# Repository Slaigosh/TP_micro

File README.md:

# TP_micro
# 1 Saisie du schéma
## 1.2 Le microcontrolleur sous KiCad
### Q13
PB9 est relié à la masse car c'est le pin boot0. 
Si le pin boot0 est relié à la masse, on boot dans la usermemory (notre code).
Si le pin boot0 est relié à Vdd, on boot dans la systemmemory (le bootloader).
Donc on veut boot dans notre code.

### Q14
L1, C5, C7 sont des composant de filtrage d'allimentation (données dans la datasheet).

## 1.3 Le reste du schéma
### Q3
Les données sont dans la page 3 de la datasheet, dans Recommended Operating Conditions.

### Q5
Les données sont dans la page 6 de la datasheet, dans AC Characteristics.

### Q6
La broche CS sert d'enable dans la communication SPI.

### Q7
C'est le pin de synchronisation du DAC.

### Q8
Il n'y a pas de MISO parce que le DAC ne communique pas au master

### Q10
C'est dans la datasheet du STLINKV3, page 19.

## 1.4 Affectation des empreintes
### Q3
0805, 009 et 1206 sont des tailles d'empreintes pour des composants passifs.
Par exemple, 0805 veut dire 8mm de longueur sur 5mm de largeur.

### Q4
LQFP, SOT-223 et SOIC sont des formes de boiter avec leur empreinte qui correspond.

# 2 Routage du circuit

# 3 Ecriture du firmware

## 3.1 Affectation des empreintes
### Q4
__STATIC_INLINE se met avant une fonction pour indiquer au compilateur de remplacer les appels de la fonction par le contenu de la fonction ( c'est comme une focntion macro).

### Q5
Si c'est une fonction INLINE dans un Header, elle est copié dans la source.

## 3.2 LED simple
### Q2
On a prit 64 car "16MHz/64=250KHz". Du coup avec une période de 255 pour le compteur du timer, on obtient environ 1KHz de période de PWR.

## 3.3 LED simple
### Q3
Pour PSC on met 64 et pour ARR 250, ce qui nous ramène à 1KHz.

### Q6
La routine d'ISR se situe dans "stm32l0xx_it.c"

### Q7
Il manque la désactivation du flag d'interruption.

### Q8
Ca va lancer l'interruption en boucle.

### Q9
Dans la routine d'interrution, il faut écrire le flag.

## 3.4 UART, un simple echo
### Q5
Il faut rajouter un & dans la ligne SerialTransmit(&ch,1);
Car il faut passer un pointeur sur le char.

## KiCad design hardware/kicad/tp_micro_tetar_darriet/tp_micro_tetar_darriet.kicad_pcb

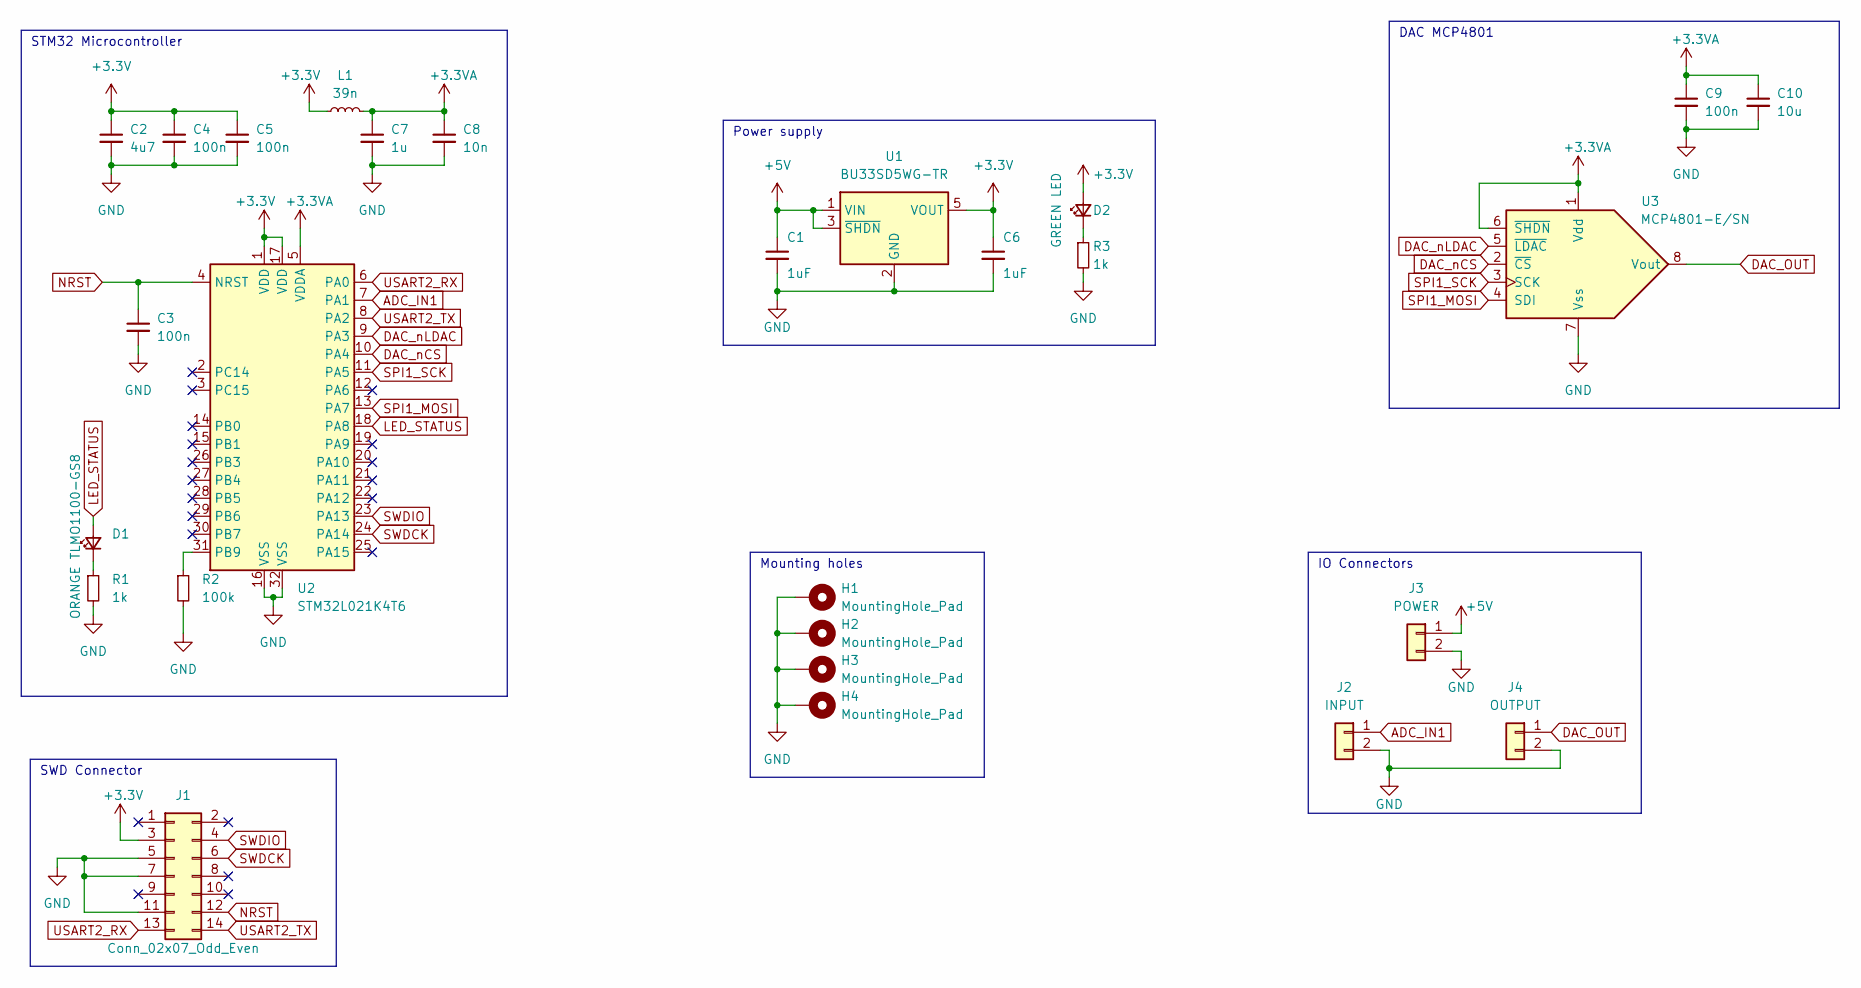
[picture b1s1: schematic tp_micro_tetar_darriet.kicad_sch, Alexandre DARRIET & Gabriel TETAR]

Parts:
C1, C6: 1uF; C_0805_2012Metric
C2: 4u7; C_0805_2012Metric_Pad1.18x1.45mm_HandSolder
C3, C4, C5, C9: 100n; C_0805_2012Metric_Pad1.18x1.45mm_HandSolder
C7: 1u; C_0805_2012Metric_Pad1.18x1.45mm_HandSolder
C8: 10n; C_0805_2012Metric_Pad1.18x1.45mm_HandSolder
C10: 10u; C_0805_2012Metric
D1: ORANGE TLMO1100-GS8; LED_0603_1608Metric_Pad1.05x0.95mm_HandSolder
D2: GREEN LED; LED_0603_1608Metric_Pad1.05x0.95mm_HandSolder
H1, H2, H3, H4: MountingHole_Pad; MountingHole_3.2mm_M3_Pad
J1: Conn_02x07_Odd_Even; PinHeader_2x07_P1.27mm_Vertical_SMD
J2: INPUT; JST_XH_B2B-XH-A_1x02_P2.50mm_Vertical
J3: POWER; JST_XH_B2B-XH-A_1x02_P2.50mm_Vertical
J4: OUTPUT; JST_XH_B2B-XH-A_1x02_P2.50mm_Vertical
L1: 39n; L_0805_2012Metric_Pad1.05x1.20mm_HandSolder
R1, R3: 1k; R_0805_2012Metric_Pad1.20x1.40mm_HandSolder
R2: 100k; R_0805_2012Metric_Pad1.20x1.40mm_HandSolder
U1: BU33SD5WG-TR; SOT-23-5
U2: STM32L021K4T6; LQFP-32_7x7mm_P0.8mm
U3: MCP4801-E/SN; SOIC-8_3.9x4.9mm_P1.27mm

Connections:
+3.3VA: C7.1, C8.1, C9.1, C10.1, L1.2, U2.5 (VDDA), U3.1 (Vdd), U3.6 (~SHDN)
+3V3: C2.1, C4.1, C5.1, C6.1, D2.2 (A), J1.3, L1.1, U1.5 (VOUT), U2.1 (VDD), U2.17 (VDD)
+5V: C1.1, J3.1, U1.1 (VIN), U1.3 (~SHDN)
ADC_IN1: J2.1, U2.7 (PA1)
DAC_OUT: J4.1, U3.8 (Vout)
DAC_nCS: U2.10 (PA4), U3.2 (~CS)
DAC_nLDAC: U2.9 (PA3), U3.5 (~LDAC)
LED_STATUS: D1.2 (A), U2.18 (PA8)
NRST: C3.1, J1.12, U2.4 (NRST)
unnamed: D1.1 (K), R1.1
unnamed: D2.1 (K), R3.1
unnamed: R2.1, U2.31 (PB9)
SPI1_MOSI: U2.13 (PA7), U3.4 (SDI)
SPI1_SCK: U2.11 (PA5), U3.3 (SCK)
SWDCK: J1.6, U2.24 (PA14)
SWDIO: J1.4, U2.23 (PA13)
USART2_RX: J1.13, U2.6 (PA0)
USART2_TX: J1.14, U2.8 (PA2)

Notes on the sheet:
DAC MCP4801
STM32 Microcontroller
Power supply
IO Connectors
Mounting holes
SWD Connector

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
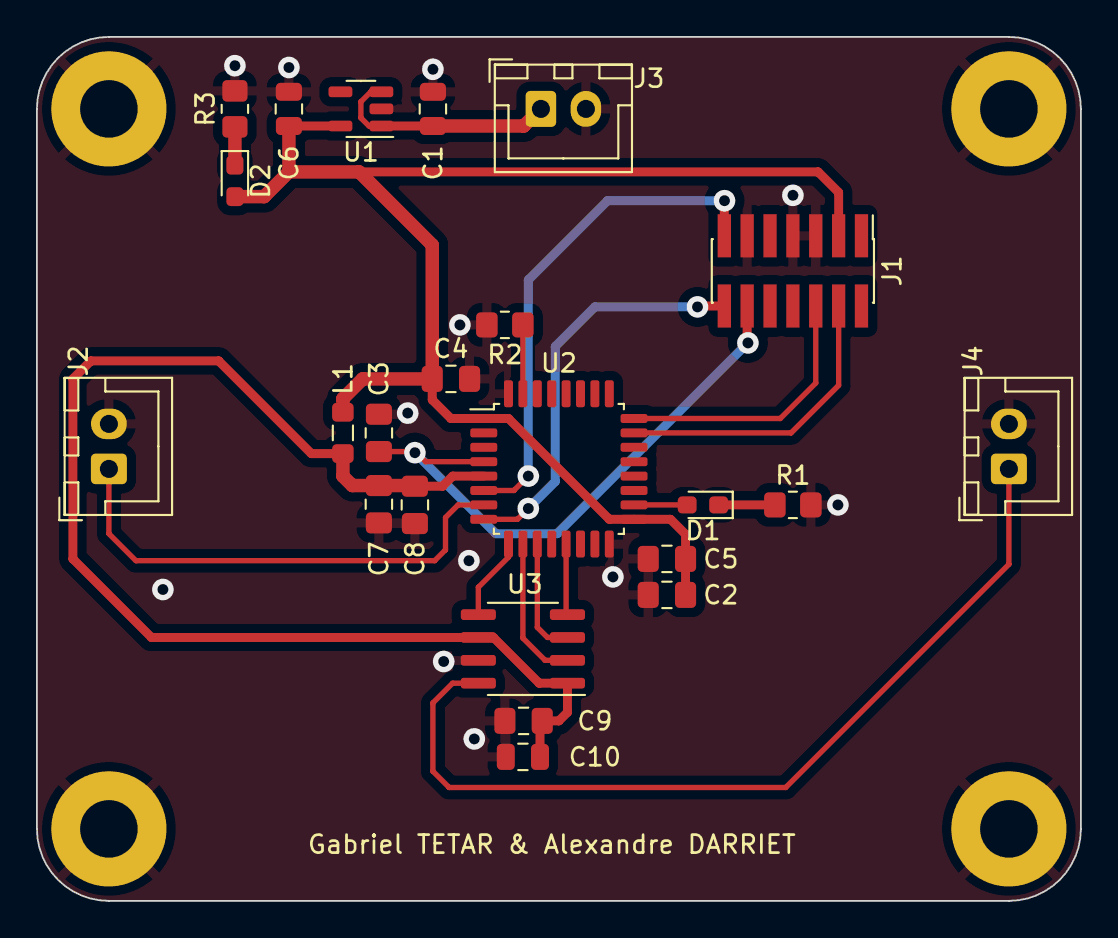
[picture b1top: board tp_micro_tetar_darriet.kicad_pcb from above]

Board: 2 copper layers, 58.0 x 48.0 mm, 27 parts (0 on the bottom side), 19 nets.

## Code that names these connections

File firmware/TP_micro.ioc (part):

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Mcu.Name=STM32L021K4Tx
Mcu.Package=LQFP32
Mcu.UserName=STM32L021K4Tx
PA0-CK_IN.Mode=Asynchronous
PA0-CK_IN.Signal=USART2_RX
PA1.Mode=IN1
PA1.Signal=ADC_IN1
PA13.Mode=Serial_Wire
PA13.Signal=SYS_SWDIO
PA14.Mode=Serial_Wire
PA14.Signal=SYS_SWCLK
PA2.Mode=Asynchronous
PA2.Signal=USART2_TX
PA3.GPIOParameters=GPIO_Label
PA3.GPIO_Label=DAC_nLDAC
PA3.Signal=GPIO_Output
PA4.Mode=NSS_Signal_Hard_Output
PA4.Signal=SPI1_NSS
PA5.Mode=Simplex_Bidirectional_Master
PA5.Signal=SPI1_SCK
PA7.Mode=Simplex_Bidirectional_Master
PA7.Signal=SPI1_MOSI
PA8.Signal=S_TIM2_CH1
RCC.HSE_VALUE=8000000
RCC.SYSCLKFreq_VALUE=16000000
RCC.SYSCLKSource=RCC_SYSCLKSOURCE_HSI
board=custom
